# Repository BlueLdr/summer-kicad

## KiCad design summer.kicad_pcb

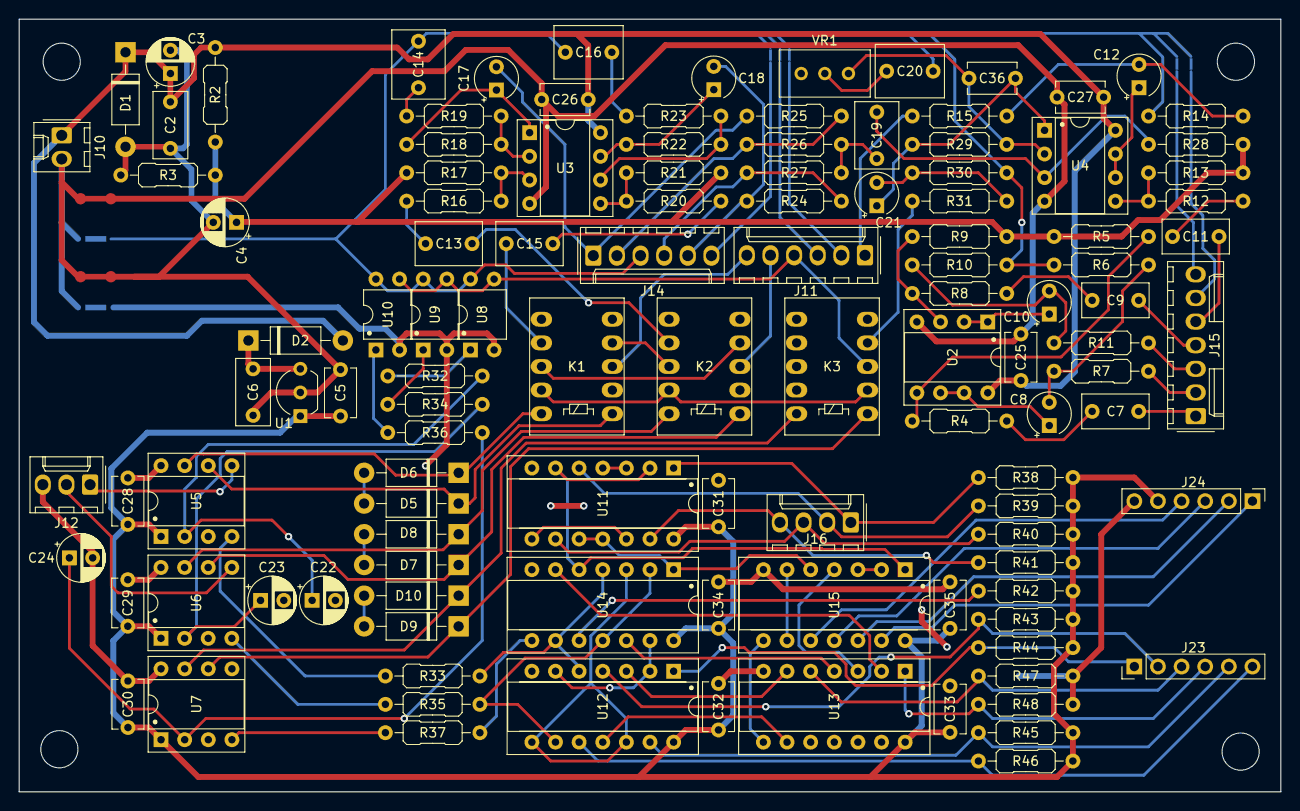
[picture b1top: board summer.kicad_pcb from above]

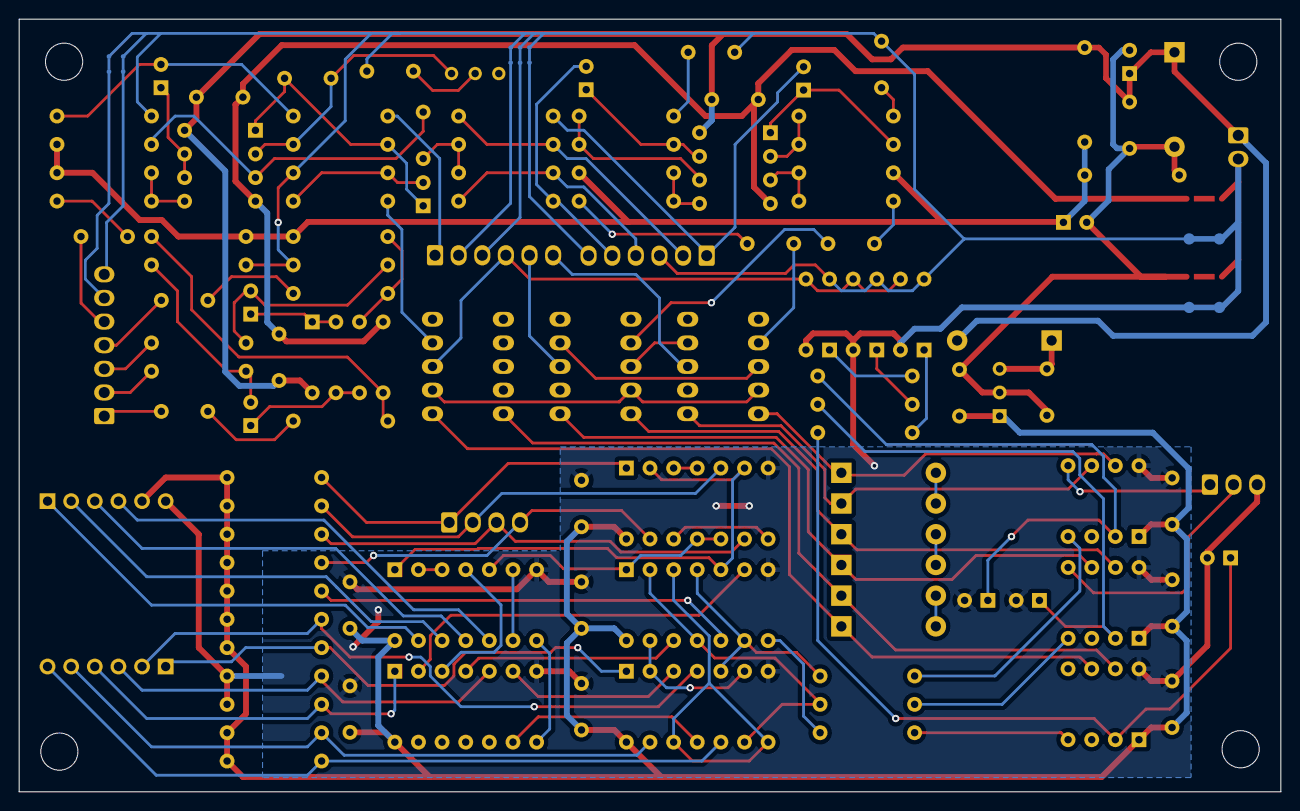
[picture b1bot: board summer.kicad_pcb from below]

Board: 2 copper layers, 135.6 x 83.1 mm, 145 parts (7 on the bottom side), 113 nets.

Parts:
C2: 47nF; C_Rect_L7.0mm_W3.5mm_P5.00mm
C3, C22, C23, C24: 100u; CP_Radial_D5.0mm_P2.50mm
C4: 47u; CP_Radial_D5.0mm_P2.50mm
C5, C25, C26, C27, C28, C29, C30, C31, C32, C33, C34, C35: 0.1uF_0603_16V; C_Disc_D5.1mm_W3.2mm_P5.00mm
C6: 0.33u; C_Rect_L7.0mm_W3.5mm_P5.00mm
C7, C9, C11: 100n; C_Rect_L7.0mm_W3.5mm_P5.00mm
C8, C10, C12, C17, C18, C21: 10uF; CP_Radial_Tantal_D4.5mm_P2.50mm
C13, C15, C19: 470n; C_Rect_L7.0mm_W4.5mm_P5.00mm
C14, C16, C20: 1uF; C_Rect_L7.2mm_W5.5mm_P5.00mm_FKS2_FKP2_MKS2_MKP2
C36: 47pF; C_Disc_D5.1mm_W3.2mm_P5.00mm
D1, D2: 1N4002; D_DO-41_SOD81_P10.16mm_Horizontal
D3, D4: LED_Dual_KKA; LEDAssy
D5, D6, D7, D8, D9, D10: 1N4733A; D_DO-41_SOD81_P10.16mm_Horizontal
HOLE1, HOLE2, HOLE3, HOLE4: MountingHole_4mm
J1: AudioJack3_Switch; ACJx-IHS_6.35mm_Audio_Jack
J2, J3: AudioJack2_Switch; ACJx-IHS_6.35mm_Audio_Jack
J4, J9: AudioJack2; ACJx-IHS_6.35mm_Audio_Jack
J5: Mag_Pre_Send; ACJx-IHS_6.35mm_Audio_Jack
J6: Mag_Pre_Return; ACJx-IHS_6.35mm_Audio_Jack
J7: Piezo_Pre_Send; ACJx-IHS_6.35mm_Audio_Jack
J8: Piezo_Pre_Return; ACJx-IHS_6.35mm_Audio_Jack
J10: Conn_01x02_Socket; Molex_KK-254_AE-6410-02A_1x02_P2.54mm_Vertical
J11, J14: Conn_01x06_Socket; Molex_KK-254_AE-6410-06A_1x06_P2.54mm_Vertical
J12: Conn_01x03_Socket; Molex_KK-254_AE-6410-03A_1x03_P2.54mm_Vertical
J15: Conn_01x07_Socket; Molex_KK-254_AE-6410-07A_1x07_P2.54mm_Vertical
J16: Conn_01x04_Socket; Molex_KK-254_AE-6410-04A_1x04_P2.54mm_Vertical
J23, J24: Conn_01x06; PinHeader_1x06_P2.54mm_Vertical
K1, K2, K3: TQ-2-5V; Relay_DPDT_FRT5
NT1, NT2, NT3, NT4: NetTie_2; NetTie24Mil
NT5, NT6, NT7, NT8, NT9: NetTie_2; NetTie10Mil
R2, R3, R6, R10, R14, R30: 100K; R_Axial_DIN0207_L6.3mm_D2.5mm_P10.16mm_Horizontal
R4, R8, R12, R16, R18, R19, R20, R22, R23, R26, R27, R29, R43, R44, R45, R46, R47, R48: 10K; R_Axial_DIN0207_L6.3mm_D2.5mm_P10.16mm_Horizontal
R5, R9, R13, R17, R21, R28: 1M; R_Axial_DIN0207_L6.3mm_D2.5mm_P10.16mm_Horizontal
R7, R11, R15: 510; R_Axial_DIN0207_L6.3mm_D2.5mm_P10.16mm_Horizontal
R24, R25: 26K; R_Axial_DIN0207_L6.3mm_D2.5mm_P10.16mm_Horizontal
R31: 470; R_Axial_DIN0207_L6.3mm_D2.5mm_P10.16mm_Horizontal
R32, R33, R34, R35, R36, R37: 1K; R_Axial_DIN0207_L6.3mm_D2.5mm_P10.16mm_Horizontal
R38, R39, R40, R41, R42: 4.7K; R_Axial_DIN0207_L6.3mm_D2.5mm_P10.16mm_Horizontal
RV1: B5K; Alpha_RV162-41
SW1, SW2: SW_Push_DPDT; Alpha_SF12020-M_DPDT_OffBoard
SW3: 3PDTBLUE; 4PDT_Blue_OffBoard
U1: L78L05_TO92; TO-92_Inline_Wide
U2, U3, U4: TL072; DIP-8_W7.62mm_Socket
U5, U6, U7: MV57; DIP-8_W7.62mm_Socket
U8, U9, U10: TLP222A; DIP-4_W7.62mm_Adjacent
U11: 7400; DIP-14_W7.62mm_Socket
U12: 74HCT74; DIP-14_W7.62mm_Socket
U13: 74HCT4075; DIP-14_W7.62mm_Socket
U14: 74HCT11; DIP-14_W7.62mm_Socket
U15: 74HCT14; DIP-14_W7.62mm_Socket
VR1: B30K; Potentiometer_Bourns_3296W_Vertical

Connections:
+5V: C5.1, C28.2, C29.2, C30.2, C31.1, C32.1, C33.1, C34.1, C35.1, J24.5, R38.1, R39.1, R40.1, R41.1, R42.2, R43.2, R44.2, R45.2, R46.2, U1.1 (VO), U5.1 (VDD), U6.1 (VDD), U7.1 (VDD), U11.14 (VCC), U12.14 (VCC), U13.14 (VCC), U14.14 (VCC), U15.14 (VCC)
+9V: C2.1, C3.1, C25.1, C26.1, C27.1, D1.1 (K), D2.2 (A), J10.1, R2.1, U2.8 (V+), U3.8 (V+), U4.8 (V+)
/Audio/MAG_BUFD: J15.3, R11.2
/Audio/MAG_IN: C9.2, J15.4
/Audio/MAG_MONO_BUFD: J15.2, R7.2
/Audio/MAG_MONO_IN: C7.2, J15.1
/Audio/PIEZO_BUFD: J11.1, R15.2
/Audio/PIEZO_IN: C11.2, J15.5
/Audio/POT_MAG_RET: J14.2, R25.2, R26.1
/Audio/POT_MAG_SEND: C17.2, J14.1, R25.1
/Audio/POT_PIEZO_RET: J14.4, R24.1, R27.2
/Audio/POT_PIEZO_SEND: C18.2, J14.5, R24.2
/Audio/SPLIT_MAG_IN: C13.1, K2.7
/Audio/SPLIT_MIX_OUT: K3.4, R31.2
/Audio/SPLIT_PIEZO_IN: C15.1, K1.7
/Jacks/MAG_IN_GND: J15.7, NT9.1
/Jacks/MAG_LOOP_GND: J11.2, NT5.1
/Jacks/OUTPUT_GND: J14.6, NT7.1
/Jacks/PIEZO_LOOP_GND: J11.3, NT6.1
/Jacks/PIEZO_PRE_RETURN: J11.5, K2.3
/Jacks/SPLIT_IN_GND: J15.6, NT8.1
/Logic/1Q: R33.2, U12.5 (Q), U14.4, U14.9
/Logic/1Qx2Q: R37.2, U14.8
/Logic/2Q: R35.2, U12.9 (Q), U14.2, U14.11
/Logic/!CLK1_RESET: J16.2, R39.2, U11.5
/Logic/!CLK1_SET: J16.1, R38.2, U11.1
/Logic/!CLK2_RESET: J16.4, R41.2, U11.13
/Logic/!CLK2_SET: J16.3, R40.2, U11.9
/Logic/DFF1_CLK: J23.3, R47.1, U13.5
/Logic/DFF1_CLR: J23.1, R44.1, U12.1 (~R)
/Logic/DFF1_PRE: J23.2, R43.1, U12.4 (~S)
/Logic/DFF2_CLK: J23.4, R48.1, U13.1
/Logic/DFF2_CLR: J23.6, R46.1, U12.10 (~S)
/Logic/DFF2_PRE: J23.5, R45.1, U12.13 (~R)
/Logic/INV1_IN: J24.3, U15.11
/Logic/INV1_OUT: J24.4, U15.10
/Logic/INV2_IN: J24.1, U15.13
/Logic/INV2_OUT: J24.2, U15.12
/Switching/MAG_LED_ON: J12.1, U5.5 (GP2)
/Switching/MAG_POST: J11.6, K1.3
/Switching/PIEZO_LED_ON: J12.2, U6.5 (GP2)
/Switching/SPLIT_AUDIO_OUT: J11.4, K3.3, U8.3, U9.3, U10.3
/Switching/SPLIT_SINGLE_OUT: K1.9, K2.9, K3.2
Earth_Clean: J10.2, NT1.1, NT2.1, NT3.1, NT4.1
GNDD: C22.2, C23.2, C24.2, C28.1, C29.1, C30.1, C31.2, C32.2, C33.2, C34.2, C35.2, J12.3, J24.6, NT3.2, R47.2, R48.2, U5.8 (VSS), U6.8 (VSS), U7.8 (VSS), U8.2, U9.2, U10.2, U11.7 (GND), U12.7 (GND), U13.7 (GND), U14.7 (GND), U15.7 (GND)
GNDPWR: C2.2, C3.2, C4.2, C5.2, C6.2, D1.2 (A), NT4.2, R3.2, U1.2 (GND)
GNDREF: C25.2, C26.2, C27.2, NT1.2, U2.4 (V-), U3.4 (V-), U4.4 (V-)
GNDS: C14.2, C16.2, C20.2, J14.3, NT2.2, NT5.2, NT6.2, NT7.2, NT8.2, NT9.2, R6.2, R10.2, R14.2, R30.2, U8.4, U9.4, U10.4
unnamed: C7.1, R4.2
unnamed: C8.2, R6.1, R7.1
unnamed: C9.1, R8.2
unnamed: C10.2, R10.1, R11.1
unnamed: C11.1, R12.2
unnamed: C12.2, R14.1, R15.1
unnamed: C13.2, R16.2
unnamed: C14.1, R19.1
unnamed: C15.2, R20.2
unnamed: C16.1, R23.1
unnamed: C17.1, R18.2, U3.1
unnamed: C18.1, R22.2, U3.7
unnamed: C19.1, R26.2, R27.1
unnamed: C21.1, C36.2, R29.2, U4.1
unnamed: C21.2, R30.1, R31.1
unnamed: C6.1, D2.1 (K), U1.3 (VI)
unnamed: D5.2 (A), D6.2 (A)
unnamed: D5.1 (K), K1.1, U5.6 (GP1)
unnamed: D6.1 (K), K1.10, U5.7 (GP0)
unnamed: D7.2 (A), D8.2 (A)
unnamed: D7.1 (K), K2.1, U6.6 (GP1)
unnamed: D8.1 (K), K2.10, U6.7 (GP0)
unnamed: D9.1 (K), K3.1, U7.6 (GP1)
unnamed: D9.2 (A), D10.2 (A)
unnamed: D10.1 (K), K3.10, U7.7 (GP0)
unnamed: K1.4, K2.8
unnamed: K1.8, K2.4
unnamed: R32.1, U8.1
unnamed: R34.1, U9.1
unnamed: R36.1, U10.1
unnamed: R42.1, U14.10
unnamed: R8.1, R9.2, U2.3 (+)
unnamed: C10.1, U2.1, U2.2 (-)
unnamed: R4.1, R5.2, U2.5 (+)
unnamed: C8.1, U2.6 (-), U2.7
unnamed: R16.1, R17.1, U3.3 (+)
unnamed: R18.1, R19.2, U3.2 (-)
unnamed: R20.1, R21.1, U3.5 (+)
unnamed: R22.1, R23.2, U3.6 (-)
unnamed: C19.2, R28.2, U4.3 (+)
unnamed: C36.1, R29.1, U4.2 (-), VR1.3 (CW)
unnamed: R12.1, R13.2, U4.5 (+)
unnamed: C12.1, U4.6 (-), U4.7
unnamed: R33.1, U5.4 (GP3)
unnamed: C22.1, R32.2, U5.2 (GP5)
unnamed: R35.1, U6.4 (GP3)
unnamed: C23.1, R34.2, U6.2 (GP5)
unnamed: R37.1, U7.4 (GP3)
unnamed: C24.1, R36.2, U7.2 (GP5)
unnamed: U11.2, U11.6, U14.5, U15.1
unnamed: U11.3, U11.4
unnamed: U11.10, U11.11, U14.1, U15.5
unnamed: U11.8, U11.12
unnamed: U12.3 (C), U13.6
unnamed: U12.2 (D), U12.6 (~Q), U14.13
unnamed: U12.11 (C), U13.9
unnamed: U12.8 (~Q), U12.12 (D), U14.3
unnamed: U13.2, U14.6
unnamed: U13.3, U15.4
unnamed: U13.4, U14.12
unnamed: U13.8, U15.8
unnamed: U15.2, U15.3
unnamed: U15.6, U15.9
unnamed: C20.1, VR1.2 (S)
Vref: C4.1, R2.2, R3.1, R5.1, R9.1, R13.1, R17.2, R21.2, R28.1

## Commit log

2023-09-03 "Initial" commit of "final" iteration
2023-09-11 Tweaks to pcb, regenerated gerber
